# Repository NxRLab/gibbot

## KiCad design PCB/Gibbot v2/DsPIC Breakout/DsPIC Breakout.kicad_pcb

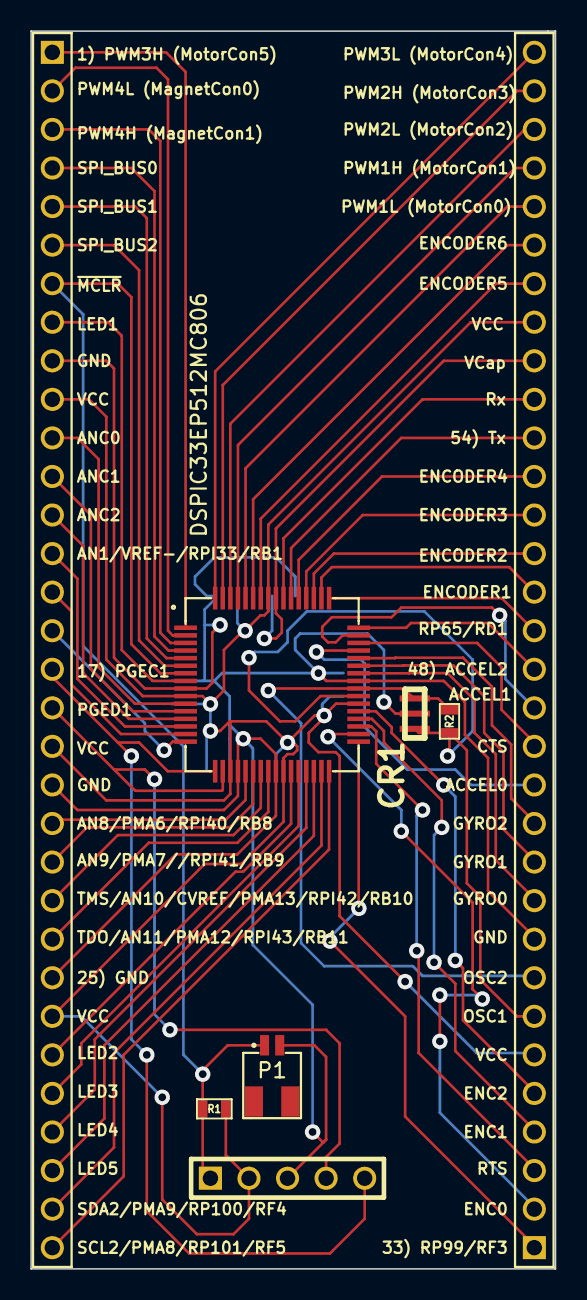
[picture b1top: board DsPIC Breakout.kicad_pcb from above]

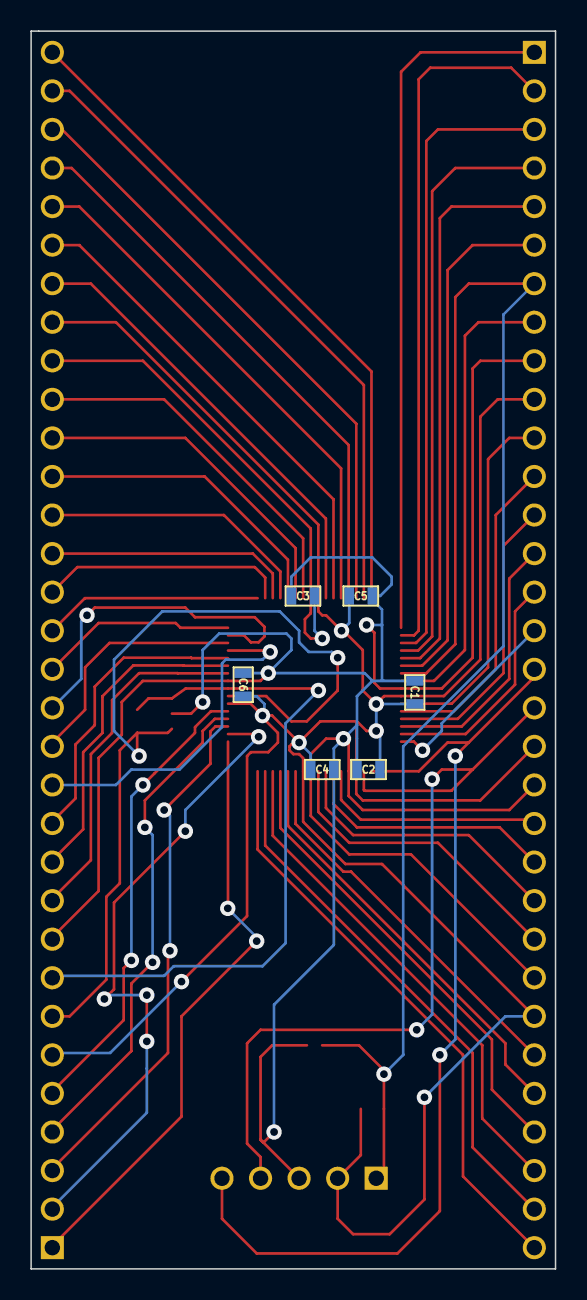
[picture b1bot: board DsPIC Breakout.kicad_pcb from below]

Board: 2 copper layers, 34.5 x 81.5 mm, 14 parts (6 on the bottom side), 57 nets.

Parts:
C1, C2, C4, C6: 0.1 uF; SM0603
C3: 10 uF; SM0603
C5: 0.1uF; SM0603
CR1: CERAMIC_RES; 8MHZ_CER_RES
J1: BREADBOARD_HEADER_32X1; PIN_ARRAY_32x1
J2: BREADBOARD_HEADER_32X1; PIN_ARRAY_32X1
P1: CONN_2; JST-1mm-2pin
P2: PROG_H; PIN_ARRAY_5x1
R1: 10K; SM0603
R2: 1M; SM0603
U1: DSPIC33EP512MC806; MY_TQFP_64

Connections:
GND: C1.1, C2.2, C3.1, C4.1, C5.1, C6.2, CR1.2, J1.9, J1.20, J1.25, J2.9, P1.2, P2.3, U1.9, U1.20, U1.25, U1.41
unnamed: J1.13, U1.13
unnamed: J1.14, U1.14
unnamed: J1.15, U1.15
unnamed: J1.16, U1.16
unnamed: J1.27, U1.27
unnamed: J1.28, U1.28
unnamed: J1.31, U1.31
unnamed: J1.7, P1.1, P2.1, R1.2, U1.7
unnamed: J1.8, U1.8
unnamed: J1.30, U1.30
unnamed: J2.5, U1.37
unnamed: J2.4, U1.36
unnamed: J2.3, U1.35
unnamed: J2.2, U1.34
unnamed: J2.1, U1.33
unnamed: J1.24, U1.24
unnamed: J2.10, U1.42
unnamed: J2.11, U1.43
unnamed: J2.12, U1.44
unnamed: J2.13, U1.45
unnamed: J2.14, U1.46
unnamed: J2.15, U1.47
unnamed: J2.16, U1.48
unnamed: CR1.3, J2.8, R2.2, U1.40
unnamed: CR1.1, J2.7, R2.1, U1.39
unnamed: J2.29, U1.61
unnamed: J2.27, U1.59
unnamed: J2.31, U1.63
unnamed: J2.26, U1.58
unnamed: J1.5, U1.5
unnamed: C3.2, J2.24, U1.56
unnamed: J1.1, U1.1
unnamed: J1.2, U1.2
unnamed: J1.3, U1.3
unnamed: J1.4, U1.4
unnamed: J1.6, U1.6
unnamed: J1.11, U1.11
unnamed: J1.12, U1.12
unnamed: J1.32, U1.32
unnamed: J2.17, U1.49
unnamed: J2.18, U1.50
unnamed: J2.19, U1.51
unnamed: J2.20, U1.52
unnamed: J2.21, U1.53
unnamed: J1.29, U1.29
unnamed: J2.22, U1.54
unnamed: J2.28, U1.60
unnamed: J2.30, U1.62
unnamed: J2.32, U1.64
unnamed: J2.23, U1.55
unnamed: J1.18, P2.4, U1.18
unnamed: J1.17, P2.5, U1.17
unnamed: J1.23, U1.23
unnamed: J1.21, U1.21
unnamed: J1.22, U1.22
VCC: C1.2, C2.1, C4.2, C5.2, C6.1, J1.10, J1.19, J1.26, J2.6, J2.25, P2.2, R1.1, U1.10, U1.19, U1.26, U1.38, U1.57

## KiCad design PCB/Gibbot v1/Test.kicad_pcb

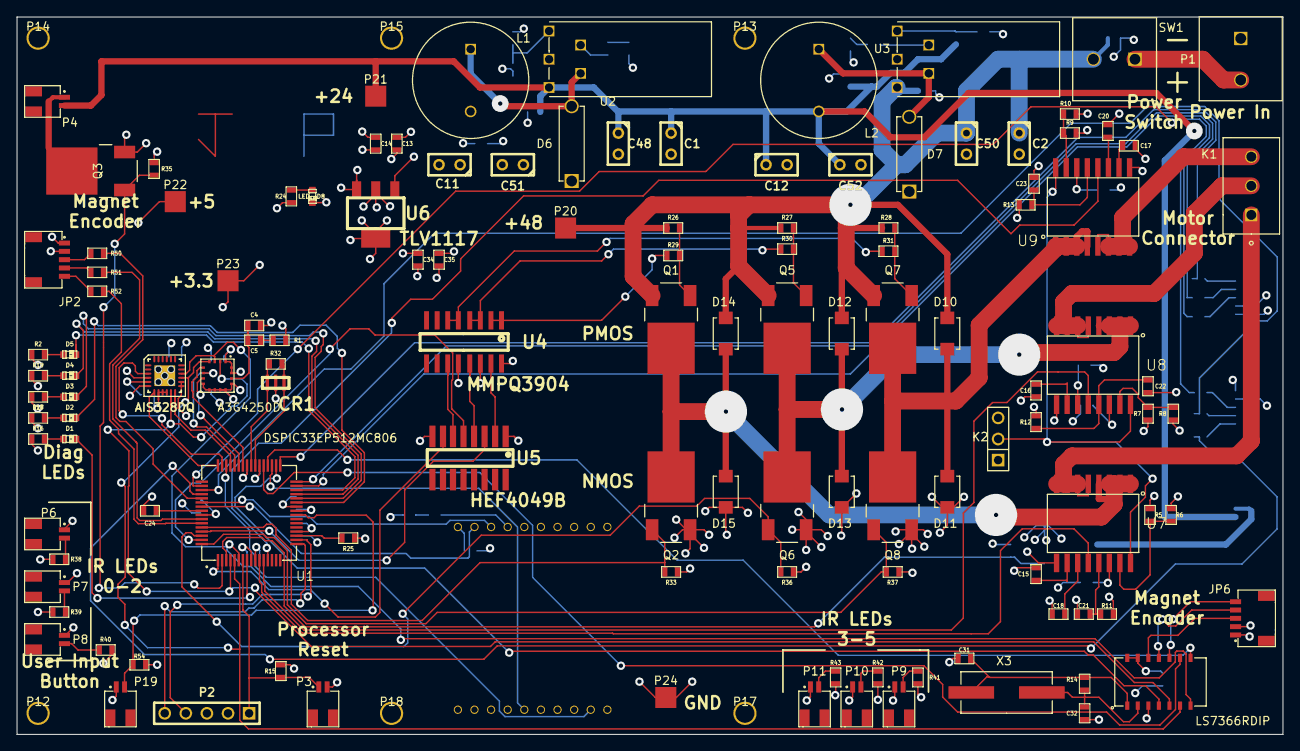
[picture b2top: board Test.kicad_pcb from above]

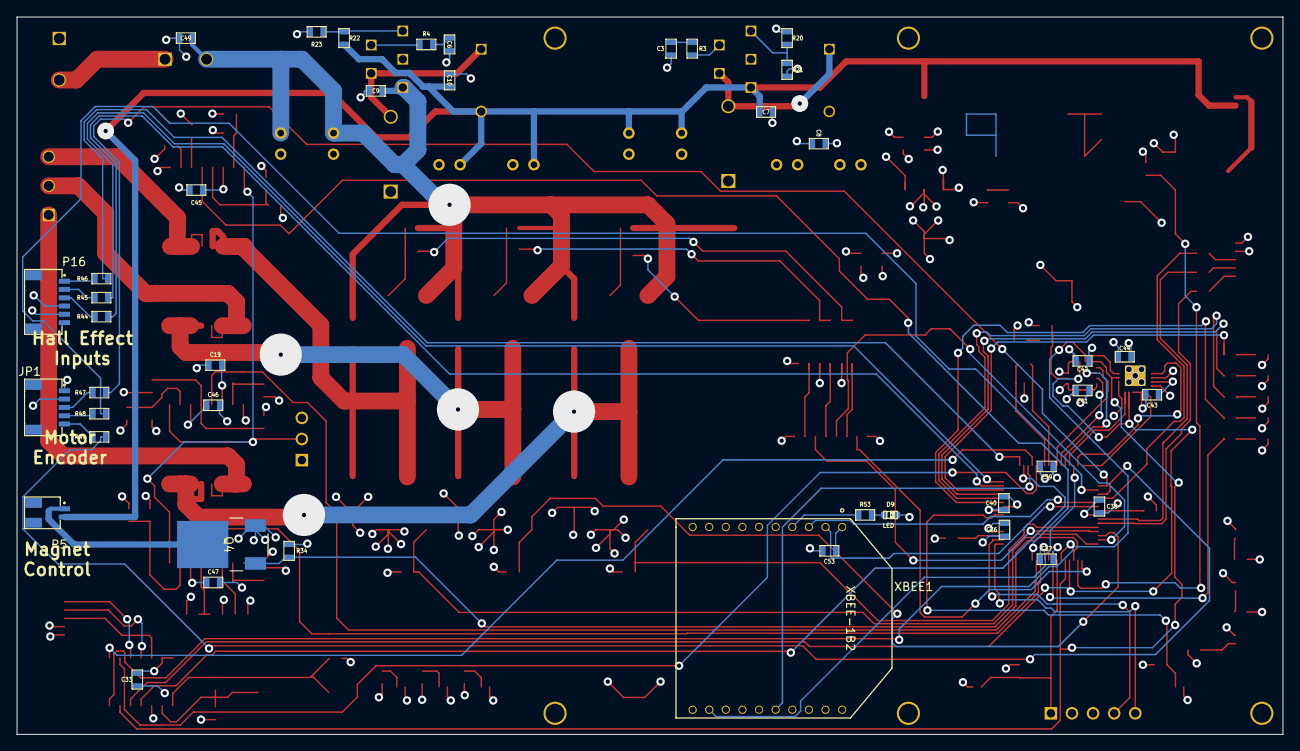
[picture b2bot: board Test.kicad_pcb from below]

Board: 4 copper layers, 152.4 x 86.4 mm, 171 parts (42 on the bottom side), 123 nets.

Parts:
ACCELEROMETER1: AIS328DQ; QFN24
C1, C2, C48, C50: 200uF; C1
C3, C6: C; SM0603
C4: 10 nF; SM0603
C5: 470 nF; SM0603
C7, C8, C9, C10, C14, C31, C32, C33, C34, C36, C37, C38, C39, C40, C41, C42, C43, C44, C45, C46, C47, C49, C53: 0.1uF; SM0603
C11, C12, C51, C52: 500uF; C1
C13, C24, C35: 10uF; SM0603
C15, C16, C17: 1nF; SM0603
C18, C19, C20, C21, C22, C23: DNI; SM0603
CR1: CERAMIC_RES; 8MHZ_CER_RES
D1, D2, D3, D4, D5, D8, D9: LED; LED-0603
D6, D7: DIODESCH; MBR340
D10, D11, D12, D13, D14, D15: DIODE; SS1H10
GYROSCOPE1: A3G4250D; LGA-16
JP1, JP2, JP6: MOT_ENC; JST-1mm-5pin
K1: CONN_3; OSTTE030161
K2: CONN_3; PIN_ARRAY_3X1
L1, L2: INDUCTOR; TSL1315
MOTOR1: LS7366RDIP; SOIC-14
P1: BATT_CONN; OSTTA020161
P2: PROG_H; PIN_ARRAY_5x1
P3, P4, P5, P6, P7, P8, P9, P10, P11, P19: CONN_2; JST-1mm-2pin
P12, P13, P14, P15, P17, P18: CONN_1; MountingHole
P16: CONN_6; JST-1mm-6pin
P20, P21, P22, P23, P24: CONN_1; TP
Q1, Q5, Q7: MOSFET_P; FDD5614P
Q2, Q3, Q4, Q6, Q8: MOSFET_N; IRLR024TRPBF
R1, R15, R26, R27, R28: 10K; SM0603
R2, R16, R17, R18, R19, R54: 1K; SM0603
R3, R4, R20, R21, R22, R23, R53: R; SM0603
R5, R6, R7, R8, R9, R10: DNI; SM0603
R11, R12, R13, R38, R39, R40, R41, R42, R43: 330; SM0603
R14, R32, R33, R34, R35, R36, R37: 1M; SM0603
R24: 320; SM0603
R25: 10; SM0603
R29, R30, R31: 30K; SM0603
R44, R45, R46, R47, R48, R49, R50, R51, R52: 2.2K; SM0603
SW1: SPST; OSTTA020161
U1: DSPIC33EP512MC806; MY_TQFP_64
U2, U3: 1074HV; TO-220-5
U4: MMPQ3904
U5: HEF4049B
U6: TLV1117
U7, U8, U9: ACS716; SOIC-16
X3: 20 MHz; ATS200CSM-1
XBEE1: XBEE-1B2; XBee

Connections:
+5V: C8.1, C11.1, C13.1, C14.1, C51.1, JP1.1, JP2.1, JP6.1, L1.2, P16.5, P22.1, R20.1, U6.1
+24V: C1.1, C7.1, C10.1, C12.1, C48.1, C52.1, L2.2, P4.2, P5.2, P21.1, R22.1, U2.5
+48V: C2.1, C9.1, C49.1, C50.1, D10.2, D12.2, D14.2, P20.1, Q1.S, Q5.S, Q7.S, R26.1, R27.1, R28.1, SW1.2, U3.5
/ACCEL0: ACCELEROMETER1.12, U1.45
/ACCEL1: ACCELEROMETER1.3, U1.47
/ACCEL2: ACCELEROMETER1.7, U1.48
/ANC0: U1.11, U7.12
/ANC1: U1.12, U8.12
/ANC2: U1.13, U9.12
/CTS: U1.46, XBEE1.12
/ENC0: MOTOR1.4, U1.34
/ENC1: MOTOR1.8, U1.36
/ENC2: MOTOR1.9, U1.37
/ENCODER1: R47.1, U1.50
/ENCODER2: R48.1, U1.51
/ENCODER3: R49.1, U1.52
/ENCODER4: R50.1, U1.53
/ENCODER5: R51.1, U1.58
/ENCODER6: R52.1, U1.59
/GYRO0: GYROSCOPE1.5, U1.42
/GYRO1: GYROSCOPE1.7, U1.43
/GYRO2: GYROSCOPE1.6, U1.44
/LED1: D1.2, U1.8
/LED2: D2.2, U1.27
/LED3: D3.2, U1.28
/LED4: D4.2, U1.29
/LED5: D5.2, U1.30
/MagnetControl0: Q3.G, R35.1, U1.2
/MagnetControl1: Q4.G, R34.1, U1.3
/MotorControl0: Q2.G, R33.1, U1.60
/MotorControl1: U1.61, U5.3
/MotorControl2: Q6.G, R36.1, U1.62
/MotorControl3: U1.63, U5.5
/MotorControl4: Q8.G, R37.1, U1.64
/MotorControl5: U1.1, U5.7
/RTS: U1.35, XBEE1.16
/RX: U1.55, XBEE1.2
/SPI_BUS0: ACCELEROMETER1.11, GYROSCOPE1.2, MOTOR1.5, U1.4
/SPI_BUS1: ACCELEROMETER1.15, GYROSCOPE1.4, MOTOR1.6, U1.5
/SPI_BUS2: ACCELEROMETER1.16, GYROSCOPE1.3, MOTOR1.7, U1.6
/TX: U1.54, XBEE1.3
/motor_control/MotorOut0: D14.1, D15.2, Q1.D, Q2.D, U7.1, U7.2, U7.3, U7.4
/motor_control/MotorOut1: D12.1, D13.2, Q5.D, Q6.D, U8.1, U8.2, U8.3, U8.4
/motor_control/MotorOut2: D10.1, D11.2, Q7.D, Q8.D, U9.1, U9.2, U9.3, U9.4
GND: ACCELEROMETER1.4, ACCELEROMETER1.6, ACCELEROMETER1.8, ACCELEROMETER1.9, ACCELEROMETER1.10, C1.2, C2.2, C3.2, C4.1, C6.2, C7.2, C8.2, C9.2, C10.2, C11.2, C12.2, C13.2, C14.2, C15.2, C16.2, C17.2, C18.2, C19.2, C20.2, C21.2, C22.2, C23.2, C24.1, C31.1, C32.1, C33.1, C34.2, C35.2, C36.2, C37.2, C38.2, C39.2, C40.2, C41.2, C42.2, C43.2, C44.2, C45.2, C46.2, C47.2, C48.2, C49.2, C50.2, C51.2, C52.2, C53.2, CR1.2, D6.1, D7.1, D8.2, D9.2, D11.1, D13.1, D15.1, GYROSCOPE1.8, GYROSCOPE1.9, GYROSCOPE1.10, GYROSCOPE1.11, GYROSCOPE1.12, GYROSCOPE1.13, JP1.2, JP2.2, JP6.2, K2.3, MOTOR1.3, P1.1, P2.3, P3.2, P6.1, P7.1, P8.1, P9.1, P10.1, P11.1, P16.4, P19.1, P24.1, Q2.S, Q3.S, Q4.S, Q6.S, Q8.S, R1.2, R6.2, R8.2, R10.2, R21.2, R23.2, R33.2, R34.2, R35.2, R36.2, R37.2, U1.9, U1.20, U1.25, U1.41, U2.3, U3.3, U4.12, U4.14, U4.16, U5.8, U6.3, U7.9, U8.9, U9.9, XBEE1.10
unnamed: P10.2, R42.2
unnamed: P11.2, R43.2
unnamed: D5.1, R2.2
unnamed: R44.1, U1.31
unnamed: R46.1, U1.33
unnamed: R45.1, U1.32
unnamed: CR1.3, R32.2, U1.40
unnamed: P19.2, R54.2, U1.24
unnamed: R53.1, XBEE1.4
unnamed: CR1.1, R32.1, U1.39
unnamed: P16.1, R46.2
unnamed: P16.2, R45.2
unnamed: P16.3, R44.2
unnamed: P7.2, R39.2
unnamed: P6.2, R38.2
unnamed: P9.2, R41.2
unnamed: P8.2, R40.2
unnamed: D9.1, R53.2
unnamed: P2.5, U1.17
unnamed: P2.4, U1.18
unnamed: JP2.5, R52.2
unnamed: JP2.4, R51.2
unnamed: JP2.3, R50.2
unnamed: JP1.3, R47.2
unnamed: JP1.5, R49.2
unnamed: JP1.4, R48.2
unnamed: P2.1, P3.1, R15.2, U1.7
unnamed: D4.1, R19.2
unnamed: D3.1, R18.2
unnamed: D2.1, R17.2
unnamed: D1.1, R16.2
unnamed: R3.1, U2.2
unnamed: C3.1, R3.2
unnamed: R20.2, R21.1, U2.1
unnamed: D6.2, L1.1, U2.4
unnamed: R22.2, R23.1, U3.1
unnamed: D7.2, L2.1, U3.4
unnamed: R25.1, U1.19
unnamed: C24.2, U1.56
unnamed: P1.2, SW1.1
unnamed: R4.1, U3.2
unnamed: C6.1, R4.2
unnamed: D8.1, R24.2
unnamed: Q5.G, R27.2, R30.1
unnamed: Q7.G, R28.2, R31.1
unnamed: Q1.G, R26.2, R29.1
unnamed: P5.1, Q4.D
unnamed: P4.1, Q3.D
unnamed: U4.13, U5.4
unnamed: U4.15, U5.2
unnamed: R31.2, U4.5, U4.6
unnamed: R30.2, U4.3, U4.4
unnamed: U4.11, U5.6
unnamed: R29.2, U4.1, U4.2
unnamed: JP6.5, MOTOR1.10
unnamed: JP6.3, MOTOR1.12
unnamed: JP6.4, MOTOR1.11
unnamed: C22.1, R12.1, U8.13
unnamed: C31.2, MOTOR1.1, R14.1, X3.2
unnamed: C32.2, MOTOR1.2, R14.2, X3.1
unnamed: C20.1, U9.11
unnamed: C5.1, R1.1
unnamed: C4.2, C5.2, GYROSCOPE1.14
unnamed: C17.1, U9.10
unnamed: K1.1, U7.5, U7.6, U7.7, U7.8
unnamed: C15.1, U7.10
unnamed: C18.1, U7.11
unnamed: K1.2, U8.5, U8.6, U8.7, U8.8
unnamed: C16.1, U8.10
unnamed: C19.1, U8.11
unnamed: K2.2, U7.16, U8.16, U9.16
unnamed: R9.1, R10.1, U9.15
unnamed: K1.3, U9.5, U9.6, U9.7, U9.8
unnamed: C23.1, R13.1, U9.13
unnamed: R5.1, R6.1, U7.15
unnamed: R7.1, R8.1, U8.15
unnamed: C21.1, R11.1, U7.13
VCC: ACCELEROMETER1.5, ACCELEROMETER1.13, ACCELEROMETER1.14, C33.2, C34.1, C35.1, C36.1, C37.1, C38.1, C39.1, C40.1, C41.1, C42.1, C43.1, C44.1, C45.1, C46.1, C47.1, C53.1, GYROSCOPE1.1, GYROSCOPE1.15, GYROSCOPE1.16, K2.1, MOTOR1.13, MOTOR1.14, P2.2, P23.1, R2.1, R5.2, R7.2, R9.2, R11.2, R12.2, R13.2, R15.1, R16.1, R17.1, R18.1, R19.1, R24.1, R25.2, R38.1, R39.1, R40.1, R41.1, R42.1, R43.1, R54.1, U1.10, U1.26, U1.38, U1.57, U5.1, U6.2, U6.4, U7.14, U8.14, U9.14, XBEE1.1

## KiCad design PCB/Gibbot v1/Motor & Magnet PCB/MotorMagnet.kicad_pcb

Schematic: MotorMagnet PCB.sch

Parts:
C2: 10uF
C5: 0.1uF
C15, C16, C17: 1nF
C18, C19, C20, C21, C22, C23: DNI
C45, C46, C47: 0.1nF
Current1, Current2, Current3: ACS716
D1: ZENER 24V
D2: ZENER 12V
D3: ZENER 5.1V
J1: BREADBOARD_HEADER_L
J2: JP5
J3: BREADBOARD_HEADER_R
K1, K2: CONN_3
LED1: D
P1: CONN_6
R1: 2.2k
R2, R17: R
R3: 360
R4: 30
R5, R6, R7, R8, R9, R10: DNI
R11, R12, R13: 330
R14, R15, R16: 2.2K
U$11: DSPIC33FJ12MC202
XBEE1: XBEE-1B2

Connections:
+5V: P1.5, R14.2, R15.2, R16.1
+48V: R2.1, R3.1, R4.1
/MotorOut0: Current1.1 (IP+), Current1.2 (IP+), Current1.3 (IP+), Current1.4 (IP+), Current2.1 (IP+), Current2.2 (IP+), Current2.3 (IP+), Current2.4 (IP+), Current3.1 (IP+), Current3.2 (IP+), Current3.3 (IP+), Current3.4 (IP+)
/PGC: J1.12, J2.5, U$11.12
/PGD: J1.11, J2.4, U$11.11
/PMCLR: J1.1, J2.1, R1.1, U$11.1
/PVCAP: C2.1, J3.6, U$11.20
/PVDD: C5.1, J1.13, J2.2, R1.2, U$11.13
/PVSS: C2.2, C5.2, J1.8, J2.3, J3.5, U$11.8, U$11.19
GND: C15.2, C16.2, C17.2, C18.2, C19.2, C20.2, C21.2, C22.2, C23.2, C45.2, C46.2, C47.2, Current1.9 (GND), Current2.9 (GND), Current3.9 (GND), D1.1, D2.1, D3.1, K2.3, LED1.2 (K), P1.4, R6.1, R8.1, R10.1, XBEE1.10 (GND)
unnamed: J1.2, U$11.2
unnamed: J1.3, U$11.3
unnamed: J1.4, U$11.4
unnamed: R17.2, XBEE1.4 (DIO8)
unnamed: J1.10, U$11.10
unnamed: J1.9, U$11.9
unnamed: Current3.5 (IP-), Current3.6 (IP-), Current3.7 (IP-), Current3.8 (IP-), K1.1
unnamed: LED1.1 (A), R17.1
unnamed: J3.10, U$11.24
unnamed: J3.11, U$11.25
unnamed: J3.12, U$11.26
unnamed: J3.13, U$11.27
unnamed: J3.14, U$11.28
unnamed: J1.14, U$11.14, XBEE1.3 (DIN/~CONFIG)
unnamed: J3.1, U$11.15, XBEE1.2 (DOUT)
unnamed: J3.7, U$11.21
unnamed: J3.8, U$11.22
unnamed: J3.9, U$11.23
unnamed: J3.4, P1.1, R16.2, U$11.18
unnamed: Current1.15 (VOC), R7.2, R8.2
unnamed: C22.1, Current1.13 (~FAULT), R12.2
unnamed: Current1.16 (FAULT_EN), Current2.16 (FAULT_EN), Current3.16 (FAULT_EN), K2.2 (PM)
unnamed: C15.1, Current2.10 (VZCR)
unnamed: C18.1, Current2.11 (FILTER)
unnamed: C21.1, Current2.13 (~FAULT), R11.2
unnamed: Current1.5 (IP-), Current1.6 (IP-), Current1.7 (IP-), Current1.8 (IP-), K1.2 (PM)
unnamed: Current2.5 (IP-), Current2.6 (IP-), Current2.7 (IP-), Current2.8 (IP-), K1.3
unnamed: C23.1, Current3.13 (~FAULT), R13.2
unnamed: Current3.12 (VIOUT), J1.5, U$11.5
unnamed: C16.1, Current1.10 (VZCR)
unnamed: C19.1, Current1.11 (FILTER)
unnamed: C20.1, Current3.11 (FILTER)
unnamed: Current2.15 (VOC), R5.2, R6.2
unnamed: C17.1, Current3.10 (VZCR)
unnamed: D3.2, R4.2
unnamed: J3.3, P1.2, R15.1, U$11.17
unnamed: D1.2, R2.2
unnamed: D2.2, R3.2
unnamed: Current1.12 (VIOUT), J1.6, U$11.6
unnamed: Current2.12 (VIOUT), J1.7, U$11.7
unnamed: J3.2, P1.3, R14.1, U$11.16
unnamed: Current3.15 (VOC), R9.2, R10.2
VCC: C45.1, C46.1, C47.1, Current1.14 (VCC), Current2.14 (VCC), Current3.14 (VCC), K2.1, R5.1, R7.1, R9.1, R11.1, R12.1, R13.1, XBEE1.1 (VDD)

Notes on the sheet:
Status LED
Hall Effect Connector
MotorOut[0..2]
3 Phase Motor Connector
Jumper to set all chips to have FAULT_EN protection
5.1V
12V
24V

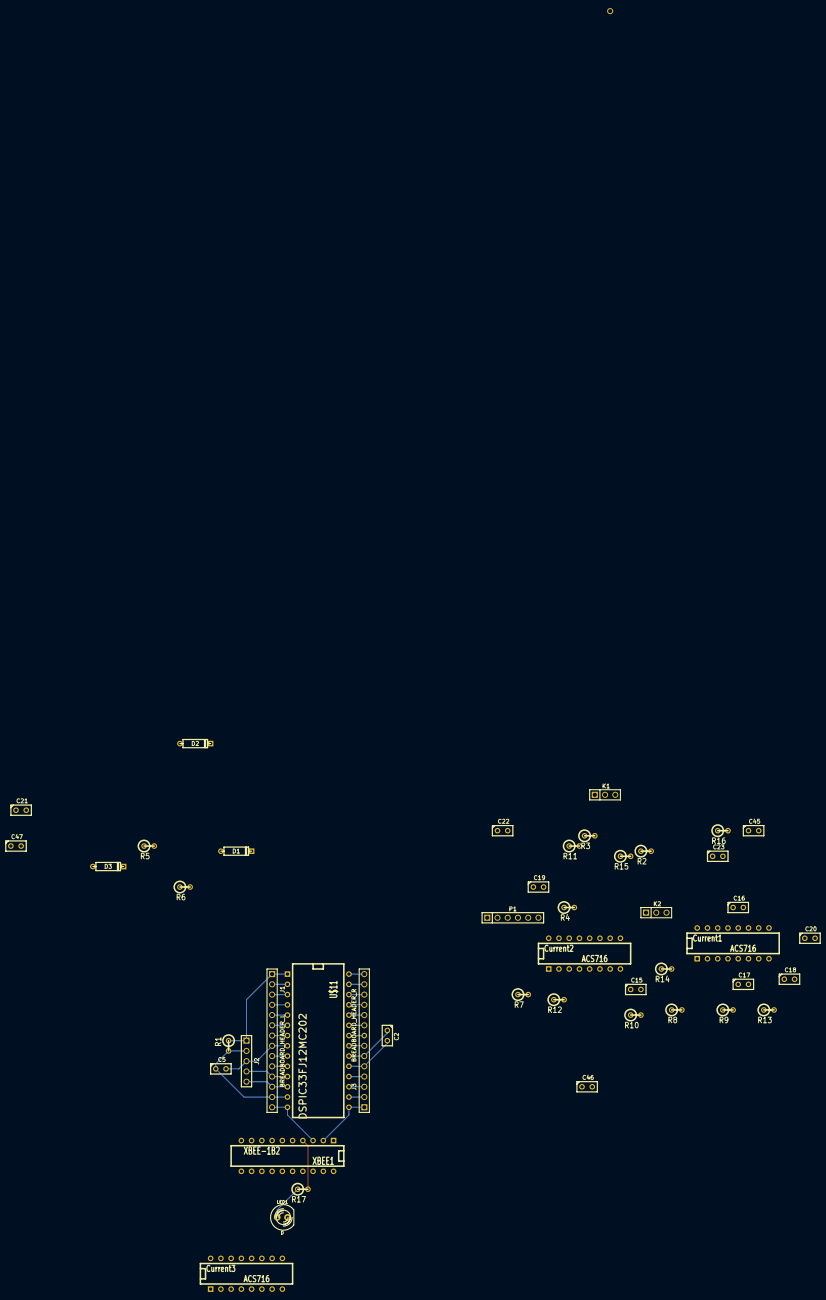
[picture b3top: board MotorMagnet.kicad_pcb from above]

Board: 2 copper layers, 46 parts (0 on the bottom side), 53 nets.

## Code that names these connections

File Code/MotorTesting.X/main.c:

/* First iteration of code to go with the Gibbot v3 board. This code
 * will be developed to interface with a python controler on the PC that
 * can drive the motor, control the moagnets and read data from the Gibbot.
 */

#include <stdio.h>
#include <stdlib.h>
#include <p33EP512MC806.h>

#include "library.h"
/* Configuration Bit Settings */
_FOSCSEL(FNOSC_FRCPLL)
//Select the internal fast RC oscilator with phase lock loop or as the clock
_FOSC(OSCIOFNC_OFF)
//OSC2 (pin 40) is clock output
_FWDT(FWDTEN_OFF)
//Watchdog timer not automatically enabled
_FICD(ICS_PGD1)
//Communicate on PGEC1 (pin 17) and PGED1 (pin 18)
_FPOR(FPWRT_PWR128)
//Wait 128ms after power on to initialize

int motoron;

int main(void) {
    //Set the calibration bits for phase lock loop
    //Clock frequency is set at 80MHz
    CLKDIVbits.PLLPRE = 0;   // N1 = 2
    PLLFBDbits.PLLDIV = 42;  // M = 44
    CLKDIVbits.PLLPOST = 0;  // N2 = 2

    TRISBbits.TRISB2 = 1;    //USER input
    //LED outputs
    TRISDbits.TRISD11 = 0;   //LED1
    TRISDbits.TRISD0 = 0;    //LED2
    TRISCbits.TRISC13 = 0;   //LED3
    TRISCbits.TRISC14 = 0;   //LED4
    //Magnet Control
    TRISDbits.TRISD10 = 0;   //Top Magnet
    TOPMAG = 1;
    
    Initialize_CN();
    Initialize_PWM();
    commutate(0);
    U1TXREG = 12;
    Lights();
    motoron = 1;
    unsigned long long i = 0;
    while (1){
        TRISBbits.TRISB2 = 1;
//        if(i > 1000000){
//            if(direction){
//                direction = 0;
//            } else{
//                direction = 1;
//            }
//            i = 0;
//        } else {
//            i++;
//        }
        if(USER){
            motoron = 1;
            direction = 1;
        }
    }
    return 0;
}

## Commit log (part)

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2013-11-14 Changes to PCBs
    Added Gibbot v4.1, a separate board for designing the charging system.
2013-11-20 Updated board size and refactored Camera.py
2013-11-26 Updates to the Gibbot v4.1 charge test board. The layout has been mostly completed. All that is left is to reroute the traces.
2013-11-27 Schematic not included in previous commit
2013-12-06 Changes to the Gibbot v4.1 PCB and the Gibbot V3.1 code. The board should now be at a point where it is ready to send to advanced circuits. The GibbotV3.1 code will respond to computer commands. The 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
2013-12-06 Cameras use angle to detect middle corner markers
2014-01-21 Updated phys params and fixed sim timing
2014-01-27 Changes to controller and DataPlotter
    Changes made by Neal and Jason, committed by Andrew. I'm not sure what
    the state of the changes is at the time of this save.
2014-01-28 Fixed simulator reset after swing-over
2014-01-30 Reorganized Python code
2014-02-03 Added Kinea Gibbot v1 Design Files
    Design files include drawings, solidworks models and pdf of specs.
2014-02-10 Added Documentation and Motor Testing Code
    Motor Testing Project file isolates motor control for debugging purposes
2014-04-02 Added Final Gibbot v4.2 Files
    Includes new library, schematic and drawing along with the cam files
    that were sent to Advanced Circuits.
2014-04-02 Cleaning up PCB folder
    Moved all of Jake's files and other early PCBs to Gibbot v1 folder.
    Moved Jason's dsPIC breakout board files to Gibbot v2 folder.
2014-04-02 Cleaning up Documentation Folder
    Moved all folders containing images into an "Images" folder. Added
    Monkeybot Report into documentation folder.
2014-04-04 New CAD Files
    New frame design in progress
2014-04-09 Adding Documentation
    Minor changes to the 1 Cell Test document, added v4 PCB documentation.
2014-04-11 Frame V3 Final
    Contains final version of frame V3. The frame CAD models will be 3D
    printed.
2014-04-28 Changes spaces to underscores
    Eliminated spaces in the names of folders within the code folder to
    prevent compiler errors.
2014-05-01 Modified frame models for 3D printing
    Wall link and motor link frames were modified to fit within the 10x10
    space of the stratasys 3d printing machine. These modified models have
    a center to center distance of 9.4in. versus the original 10.5in.
    distance.
2014-05-09 Wixel Code
2014-05-12 Updates to Primary and Secondary Code
    Test functions are fully functional. Error handling still needs to be
    built into I2C code to allow it to function with electrical noise.
2014-05-16 updated dsPIC code for wixel
    Fixed uart problems
2014-05-30 Updates to Wixel Code
    Changes to code related to communication and interface and updated
    current ISR
2014-06-10 Final Design of V5 Board
    Contains the final version of the V5 schematic and board files. Also
    contains the CAM files that were sent to AC. Also contains updates to
    PrimaryV4 dsPIC code and the V5 documentation.
2014-06-30 Documentation on V5 PCB ADC Issue
    There is an offset for some reason on the V5 PCB ADC current sensor.
    This documents problem and testing done.
2014-07-01 Changed location of V5 Code
2014-07-01 splitting old wixel code and new wixel code into separate folders. The newer code serves as a template for writing wireless and uart communication between the wixels or a wixel and PC. The older code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
2014-07-01 added feedback on read_string function.
2014-07-03 added comments to wixel-related code.
2014-07-03 Fixed conflict in comments
2014-07-07 Initial commit for java GUI files
2014-07-07 Local changes
2014-07-08 Worked on CurrentSwipeTab and reorganized some files. NxRBananaPanel1 replaced by GibbotGUI.
2014-07-08 an alternative version to rxtx for java serial communication.
2014-07-10 added code for better swipe tabs and data graph animation
2014-07-14 added GUISerialPort to GUI; successfully communicated w/ nu32 and translated to graphics
2014-07-17 clean beta version w/ initial drawing bugs fixed and unified timer. will be moving on to gui2 after this
2014-07-21 Resolving Conflicts for PIC code
2014-07-21 switched to working in gui2, with better graphics and basic functionality
2014-07-22 Wixel Documentation
    Updated documentation for motor encoder
2014-07-23 Uncommented the command enabling QEI2 so we can use the wall encoder.
2014-07-28 added serial funtionality to swipe tabs, cleaned up unused files
2014-07-31 Updated PIC to PC communication
    Included both string and data stream versions of communication and fixed
    a UART read issue for the MPU
2014-08-06 Added awake/asleep modes to GUI, put required images into "imagefiles", added comments to all classes and deleted unused ones.
2014-08-11 PCB V6
    Added control board files (primary and secondary) and the gerber files
    used to create board, as well as the LED board files.
2014-08-11 Motor Drive PCB
    added motor driver eagle files to PCB V6 folder
2014-08-11 Made layout more compatible with screen size changes.
2014-08-14 Got rid of most magic numbers, replaced with constants.
2014-08-20 added java files and JCreator files to ignore
2014-08-20 gitignore file
2014-08-20 2nd try
2014-08-20 took 2 files off stage
2014-08-20 Debugger gui now works at high speed and graphs with color. Scale function not working for some reason.
2014-11-03 Added QEI interrupt to dsPIC code
2015-01-06 Adding gibbot and motor models. Still a work in progress, but almost done.
2015-01-19 adding script used to run gui3 Java code. Not sure what $1 does in script.
2015-01-22 testing a conflict scenario.
2015-01-22 finalizing example.txt code for conflict test.
2015-01-22 removing MPLAB X autogenerated folders and files.
2015-01-22 deleting file, going to test restoring to older version.
2015-01-22 Revert "removing MPLAB X autogenerated folders and files."
    This reverts commit 0cb8b47b800bff81e2d9527c2033c72629525d9a.
2015-01-23 starting point for JNI code.
2015-01-23 learning how to modify file
2015-01-23 Craig is learning
2015-01-23 Change to number 20
    I felt that this change was necessary.
2015-01-23 Example modification
2015-01-23 fixing error
2015-01-23 creating new file test
2015-01-23 test delete
2015-01-24 .
    .
2015-01-24 added gitattributes to fix line endings across files.
2015-01-25 Adding files
    Added compiled versions of arrays.cpp (arrays.exe)
    Uncommented arrays.cpp
    Duplicated Arrays and named CameraJNI.java
    Duplicated arrays and named camerajni.cpp
    Added header file of CameraJNI.h
2015-01-26 Getting code runnning on Jeanette's computer with Eclipse
2015-01-27 Produced header file from CameraJNI
2015-01-27 Intro Board
    Intro Board
2015-01-27 New Board Schematic
    added new schematic
2015-01-29 Adding jungle background to official git code
2015-01-30 double-checked motor values.
2015-01-30 adding howto to talkingPIC code.
2015-01-30 Hannah PIC Projects
2015-01-30 moved into intro folder
2015-01-30 V7 and Battery Manager Boards
    Added RPP and diodes to control boards and finished battery manager
    layout
2015-02-02 Figured out the problem of not adding new images See ImageHandler.java class
2015-02-02 Battery Manager Protection
    added protection diodes to battery manager board
2015-02-02 Organized files and updated code
2015-02-02 Updated mainV6.c and time.c in motor test
2015-02-02 V7 Board print board and gerber files
    Primary and secondary boards on one board for gerber files
2015-02-03 Fixed motor control
2015-02-03 adding candidate C++ matrix library/linear algebra solve Eigen3
2015-02-07 Added test JavaScript game to page "Games"
2015-02-09 test_motor update
    pseudocode for test_motor()
2015-02-10 New website design
2015-02-12 mainV6.c update
    Implemented commend u, d, and m (for increasing/decreasing duty and
    turning off the motor)
2015-02-12 First pages commit
2015-02-12 modified test code to switch lower and bottom magnets. MMA nb have no real changes to report.
2015-02-13 Figured out why the original code ran so slow. In every call of repaint() in the CurrentBox, HardwareBox, and SpeedometerBox the shadow border behind them was re-drawn.
2015-02-13 adding comment to mark as current file
2015-02-13 30ms interrupt to test encoders, fixed bug in encoder.c
2015-02-13 More encoder testing
2015-02-16 added images
2015-02-16 Updated encoder testing with the option to save to a global array
2015-02-16 delay
    look into __delay32() function
2015-02-17 Correct motion equations for Gibbot.java's arcMotionUpdate()
2015-02-17 changed logo
2015-02-17 Added quiz page, Gibbon facts page, linked index
2015-02-17 Linked QuizPage to index
2015-02-17 Updated Battery level in SpeedometerBox.java
2015-02-17 Fixed error in test_swing/time.c to prep for swinging testing
2015-02-17 Updates to wireless control in test_swing
2015-02-18 Small changes to test_swing
2015-02-20 modified code to try and debug why the robot wasn't working. verified that dsPIC is no longer outputting 3.3 V on PWM channels and that default value at startup was to have the bottom magnet on (this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
2015-02-23 Added photos
2015-02-23 photos loading 2
2015-02-23 phtoo 5
2015-02-23 one page gibbon info
2015-02-24 gibbot one page
2015-02-24 color fix
2015-02-24 nav fixed
2015-02-24 changed index name
2015-02-24 Current Control files
2015-02-24 H-bridge changes 2-24
2015-02-24 rando text
2015-02-24 make scalable on phone
2015-02-24 size of quizzes
2015-02-25 modified main so that it print encoder values
2015-02-27 Deleting Files
    Deleting Extra Files
2015-03-01 PCB V8 and V7 changes
    Added V8 (broken-up) boards and minor updates to V7 boards.
2015-03-02 Library of control functions
2015-03-02 Gradient Descent
    Now only works with single variable functions
2015-03-02 Adding a README for setting up a Visual Studio project using the Camera SDK and Java JDK.
2015-03-03 nav buttons
2015-03-03 phone zoom works
2015-03-03 Updated current control with Matlab communications
2015-03-03 Testing Data
2015-03-03 Matlab control menu code
2015-03-03 spacing
2015-03-03 nav buttons 1
2015-03-03 Merge branch 'gh-pages' of https://github.com/nxrlab/gibbot into gh-pages
    Conflicts:
    QuizPage.html
    images/portfolio/Gibbot_0012(2).jpg
    images/portfolio/file000277439881.jpg
    images/portfolio/gibbon.jpg
    index.html
2015-03-03 Undoing the test committing
2015-03-04 Consolidated all Control work in gibbot/Controls
2015-03-04 Data for Wall test
2015-03-05 Redid swing control argument communication with malloc
2015-03-05 Order-Ready board
    Increased thickness of connections next to choke inductors. Added test
    points. Moved C10 closer to chips.
2015-03-05 Minor Changes
    Added transformers and test points for GPIO
2015-03-05 Final Final Board
    Increased a few trace sizes. edited the polygon in the top right corner
2015-03-06 Input modifications to swing.X
2015-03-07 attempting to make images file load relative to where gui4 java project is being invoked from. assuming it is top-leve gui4 directory. must be tested against what the IDE actually does.
2015-03-08 changed file type of aspic pinout image
2015-03-09 1. Fixed hardcoding of fonts on TextBox and Speedometer and TorqueBox so they should fit onto larger screens better. May have to redo to take height into account (currently only doing width)
    2. Copied back old code from LayoutContainerPanel2 because of bug found
    during beta test - will go through it again
    3. Changed jungle image because it was sideways the whole time and no
    one noticed...not even the beta testers
2015-03-09 Fixed spacing between lines in TextBox
2015-03-09 Fixed resizing and position of gibbotBubble and bananaBubble
2015-03-10 Adjustments to control library
2015-03-10 Quiz Page update
    Corrected the navigation bar
    adjusted buffer zone between quizzes
2015-03-10 changes from beta test
2015-03-10 animations added
2015-03-10 Transform and Cluster functions
    just adding some vision code :)
2015-03-12 Finished ControlLib restructuring
2015-03-13 Moved power connector on V8 primary board
    Connector was too close to edge and would not fit in frame properly
2015-03-16 Current control menu updates
2015-03-20 Current menu updates moved to primary files
2015-03-21 A couple more edits to vision code
    code is theoretically complete but running in to JNI error that wasn't
    encountered before
2015-04-04 finished writing dsPIC inter-board communication code. Originally was going to do DMA, but it wasn't working and there are synchornization issues even if it did so switched to simpler read/write_pic_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
2015-04-04 adding Makefile. Need a way to make sure that it is not overwritten if mulitple people start using it.
2015-04-04 Commenting Code
